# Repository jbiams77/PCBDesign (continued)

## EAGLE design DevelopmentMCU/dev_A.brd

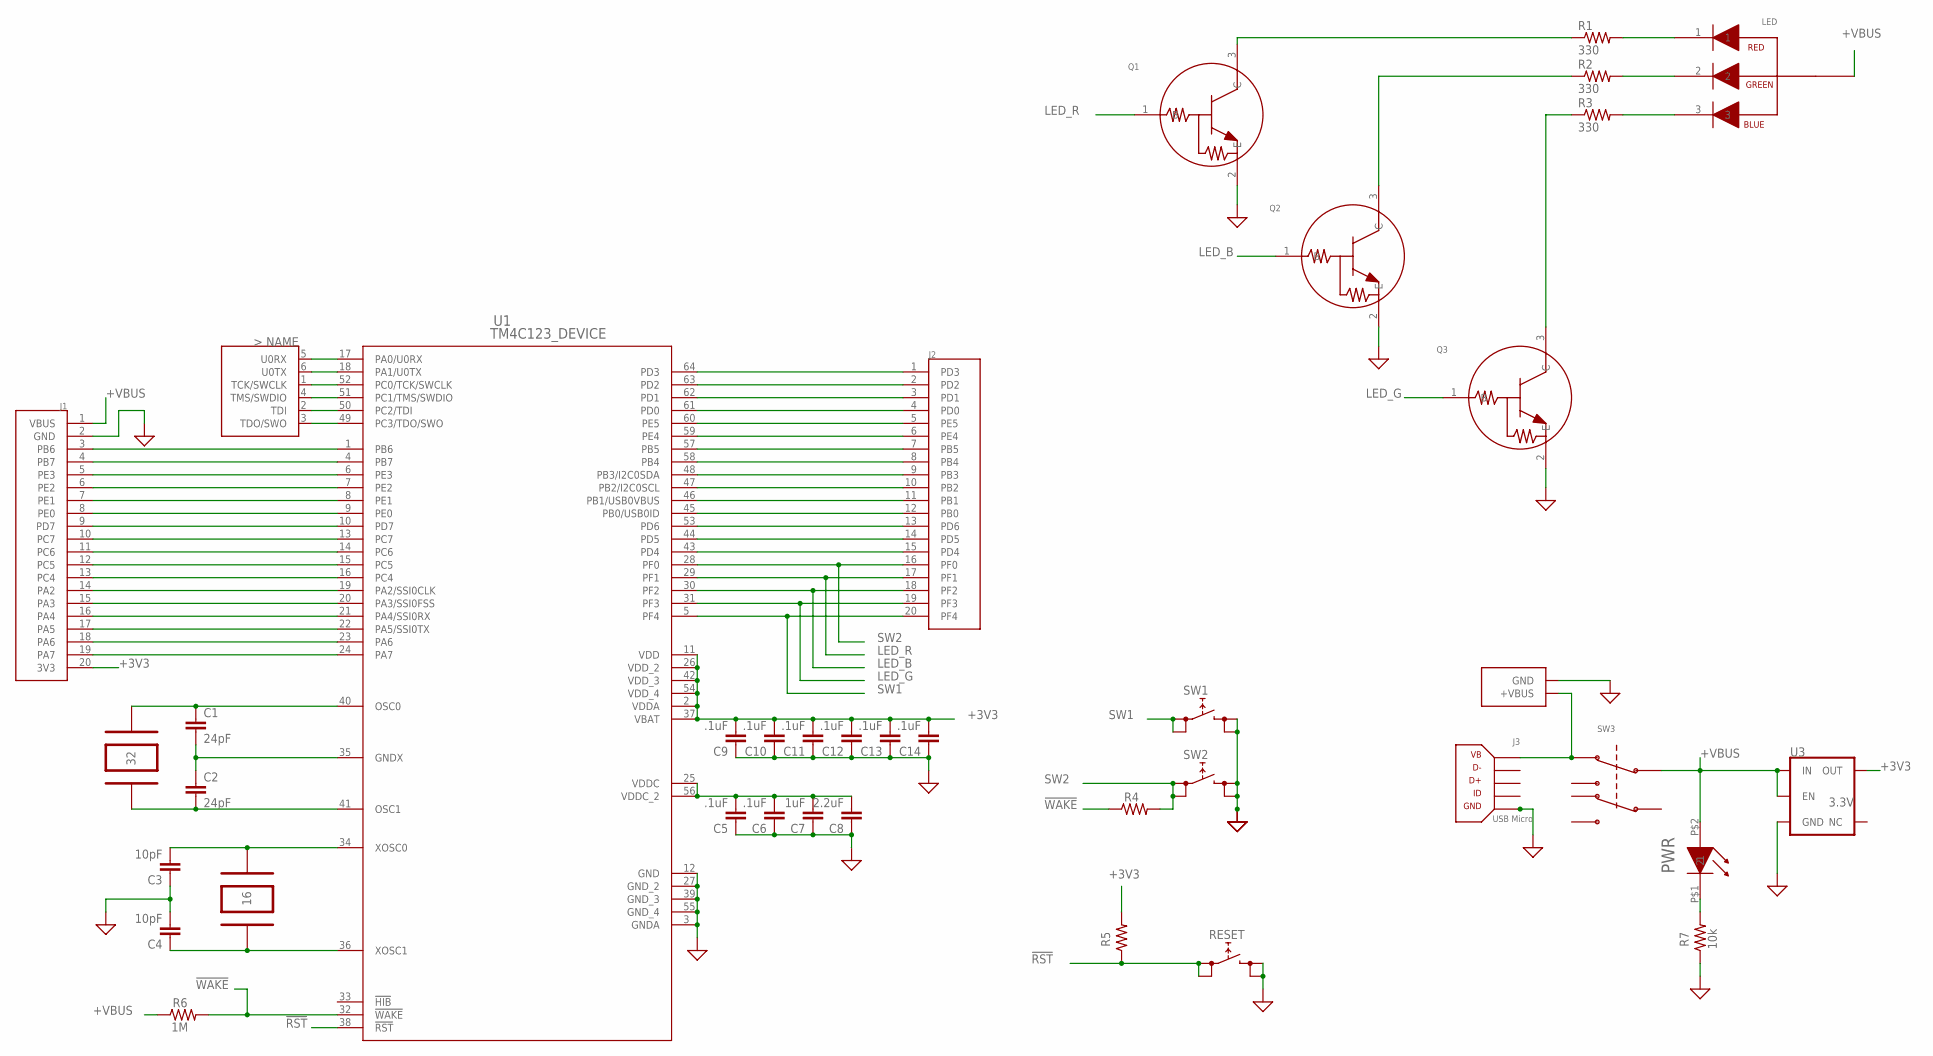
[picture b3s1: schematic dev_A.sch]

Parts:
C1, C2: 24pF; CAPC1005X35N
C3, C4: 10pF; CAPC1005X35N
C5, C6, C9, C10, C11, C12, C13, C14: .1uF; CAPC1005X35N
C7: 1uF; CAPC1005X35N
C8: 2.2uF; CAPC1005X35N
DEBUG: JTAG; HDRV6W64P254_2X3_800X508X838B
J1: HEADER_J1; HDRV20W80P254_1X20_5100X250X838B
J2: HEADER_J2; HDRV20W80P254_1X20_5100X250X838B
J3: USBMICRO; USBMICROB
LED: RGBLED
PWR: LED_511
Q1, Q2, Q3: NPN_BJT; SOT416
R1, R2, R3: 330; CAPC1005X35N
R4, R5: RESISTOR; CAPC1005X35N
R6: 1M; CAPC1005X35N
R7: 10k; CAPC1005X35N
RESET: SWITCH_B3S; SW_BS3
SW1, SW2: SWITCH_B3S; SW_BS3
SW3: JS202011SCQN; SW_JS202011SCQN
U1: TM4C123_DEVICE; TM3C123_FOOTPRINT
U3: 3.3V; SOT23-5
VBUS: POWER; HDRV2W64P254_1X2_600X300X838B
Y1: 32kHz; GHI2_CRYSTAL_3.2X1.5
Y2: Y2; CRYSTAL_16MHZ

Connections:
!RST: R5.1, RESET.1, RESET.2, U1.38 (!RST)
!WAKE: R4.1, R6.2, U1.32 (!WAKE)
+3V3: C9.2, C10.2, C11.2, C12.2, C13.2, C14.2, J1.20 (3V3), R5.2, U1.2 (VDDA), U1.11 (VDD), U1.26 (VDD_2), U1.37 (VBAT), U1.42 (VDD_3), U1.54 (VDD_4), U3.5 (OUT)
+VBUS: J1.1 (VBUS), LED.4, PWR.P$2 (2), R6.1, SW3.2, U3.1 (IN), U3.3 (EN)
+VBUS_IN: J3.VB (1), SW3.1, VBUS.1 (+VBUS)
GND: C3.1, C4.2, C5.1, C6.1, C7.1, C8.1, C9.1, C10.1, C11.1, C12.1, C13.1, C14.1, J1.2 (GND), J3.0 (GND), J3.01 (GND), J3.02 (GND), J3.03 (GND), J3.GND, Q1.2 (E), Q2.2 (E), Q3.2 (E), R7.1, RESET.3, RESET.4, SW1.3, SW1.4, SW2.3, SW2.4, U1.3 (GNDA), U1.12 (GND), U1.27 (GND_2), U1.39 (GND_3), U1.55 (GND_4), U3.2 (GND), VBUS.2 (GND)
LED_B: J2.18 (PF2), Q2.1 (B), U1.30 (PF2)
LED_G: J2.19 (PF3), Q3.1 (B), U1.31 (PF3)
LED_R: J2.17 (PF1), Q1.1 (B), U1.29 (PF1)
unnamed: J1.5 (PE3), U1.6 (PE3)
unnamed: J1.6 (PE2), U1.7 (PE2)
unnamed: J1.7 (PE1), U1.8 (PE1)
unnamed: J1.8 (PE0), U1.9 (PE0)
unnamed: J1.9 (PD7), U1.10 (PD7)
unnamed: J1.10 (PC7), U1.13 (PC7)
unnamed: J1.11 (PC6), U1.14 (PC6)
unnamed: J1.12 (PC5), U1.15 (PC5)
unnamed: J1.13 (PC4), U1.16 (PC4)
unnamed: J1.14 (PA2), U1.19 (PA2/SSI0CLK)
unnamed: J1.15 (PA3), U1.20 (PA3/SSI0FSS)
unnamed: J1.16 (PA4), U1.21 (PA4/SSI0RX)
unnamed: J1.17 (PA5), U1.22 (PA5/SSI0TX)
unnamed: J1.18 (PA6), U1.23 (PA6)
unnamed: J1.19 (PA7), U1.24 (PA7)
unnamed: J2.15 (PD4), U1.43 (PD4)
unnamed: J2.14 (PD5), U1.44 (PD5)
unnamed: J2.13 (PD6), U1.53 (PD6)
unnamed: J2.12 (PB0), U1.45 (PB0/USB0ID)
unnamed: J2.11 (PB1), U1.46 (PB1/USB0VBUS)
unnamed: J2.10 (PB2), U1.47 (PB2/I2C0SCL)
unnamed: J2.9 (PB3), U1.48 (PB3/I2C0SDA)
unnamed: J2.8 (PB4), U1.58 (PB4)
unnamed: J2.7 (PB5), U1.57 (PB5)
unnamed: J2.6 (PE4), U1.59 (PE4)
unnamed: J2.5 (PE5), U1.60 (PE5)
unnamed: J2.4 (PD0), U1.61 (PD0)
unnamed: J2.3 (PD1), U1.62 (PD1)
unnamed: PWR.P$1 (1), R7.2
unnamed: LED.1, R1.2
unnamed: LED.2, R2.2
unnamed: LED.3, R3.2
unnamed: Q3.3 (C), R3.1
unnamed: Q2.3 (C), R2.1
unnamed: Q1.3 (C), R1.1
unnamed: C1.1, U1.40 (OSC0), Y1.P$2 (2)
unnamed: C2.2, U1.41 (OSC1), Y1.P$1 (1)
unnamed: C1.2, C2.1, U1.35 (GNDX)
unnamed: C3.2, U1.34 (XOSC0), Y2.2
unnamed: C4.1, U1.36 (XOSC1), Y2.1
unnamed: DEBUG.5 (U0RX), U1.17 (PA0/U0RX)
unnamed: DEBUG.6 (U0TX), U1.18 (PA1/U0TX)
unnamed: DEBUG.1 (TCK/SWCLK), U1.52 (PC0/TCK/SWCLK)
unnamed: DEBUG.4 (TMS/SWDIO), U1.51 (PC1/TMS/SWDIO)
unnamed: DEBUG.2 (TDI), U1.50 (PC2/TDI)
unnamed: DEBUG.3 (TDO/SWO), U1.49 (PC3/TDO/SWO)
unnamed: J2.2 (PD2), U1.63 (PD2)
unnamed: J2.1 (PD3), U1.64 (PD3)
PB6: J1.3 (PB6), U1.1 (PB6)
PB7: J1.4 (PB7), U1.4 (PB7)
SW1: J2.20 (PF4), SW1.1, SW1.2, U1.5 (PF4)
SW2: J2.16 (PF0), R4.2, SW2.1, SW2.2, U1.28 (PF0)
VDDC: C5.2, C6.2, C7.2, C8.2, U1.25 (VDDC), U1.56 (VDDC_2)

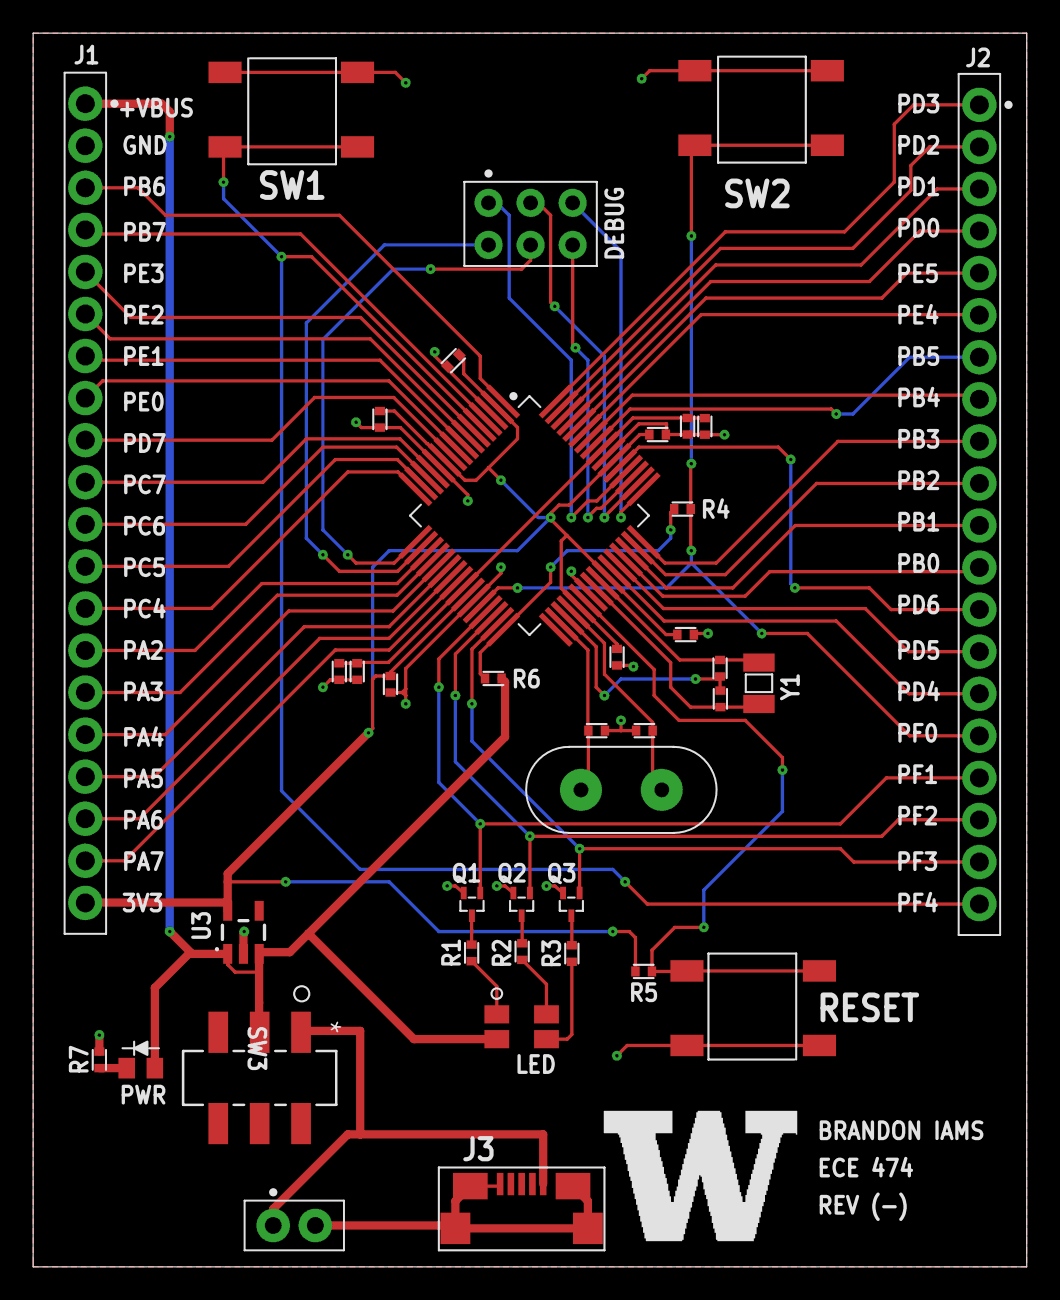
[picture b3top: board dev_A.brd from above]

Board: 2 copper layers, 60.0 x 74.5 mm, 40 parts (0 on the bottom side), 62 nets.

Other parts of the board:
U$1: LOGO

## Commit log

2019-10-14 Library almost finished
2019-10-16 second commit
2019-10-17 Staging
2019-10-28 Movingn to PC
2019-11-04 Started on the Fill Control Design, finished with dev MCU
2019-11-06 transferring to PC
2019-11-08 Push cad to pc
2019-11-08 stage
2019-11-08 reset
2019-11-08 push to laptop
2019-11-12 starting on final
2019-11-14 Ready for layout
2019-11-15 to pc
2019-11-15 to surface
2019-11-16 merge
2019-11-16 done
2019-11-16 fixing...
